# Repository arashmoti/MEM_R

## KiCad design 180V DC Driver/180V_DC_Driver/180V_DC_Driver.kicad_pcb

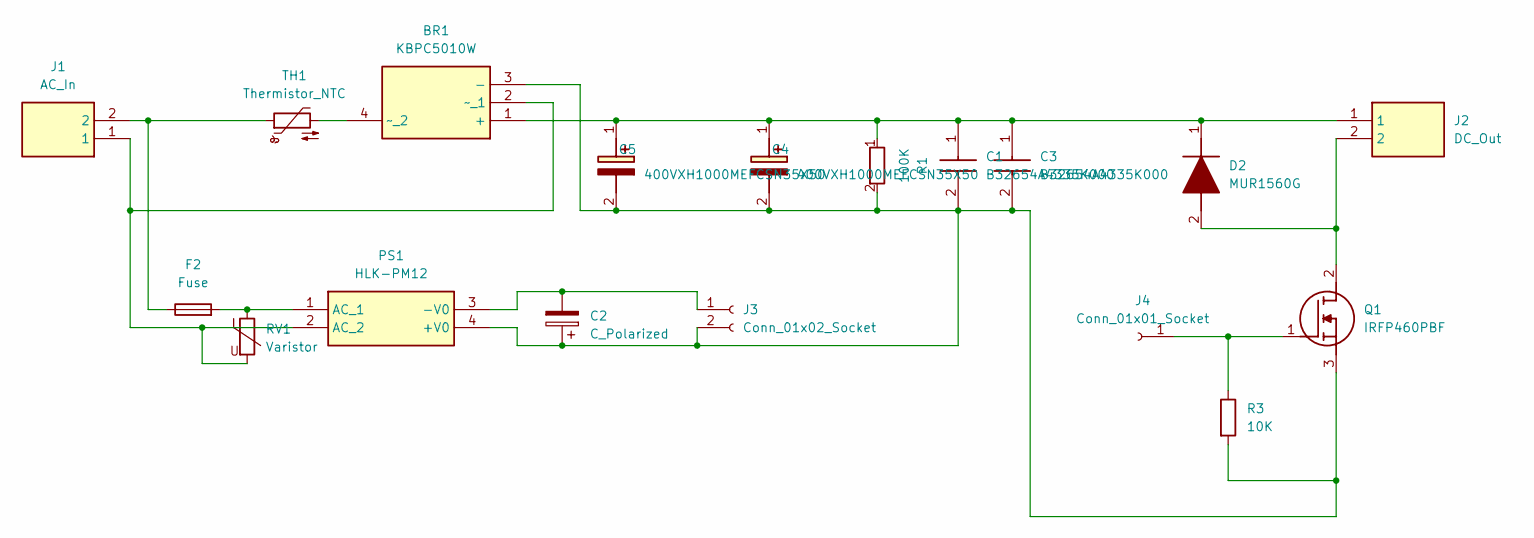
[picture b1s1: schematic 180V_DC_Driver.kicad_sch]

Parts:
BR1: KBPC5010W; Diode_Bridge_28.6x28.6x7.3mm_P18.0mm_P11.6mm; Manufacturer_Part_Number KBPC5010W; Mouser Part Number 905-KBPC5010W
C1, C3: B32654A4335K000; C_Rect_L31.5mm_W13.0mm_P27.50mm_MKS4; Manufacturer_Part_Number B32654A4335K000; Mouser Part Number 871-B32654A4335K
C2: C_Polarized; CP_Radial_D6.3mm_P2.50mm
C4, C5: 400VXH1000MEFCSN35X50; CP_Radial_D35.0mm_P10.00mm_SnapIn; Manufacturer_Part_Number 400VXH1000MEFCSN35X50
D2: MUR1560G; TO-220-2_Vertical; Manufacturer_Part_Number MUR1560G; Mouser Part Number 863-MUR1560G
F2: Fuse; PinHeader_1x02_P2.54mm_Vertical
J1: AC_In; TerminalBlock_Phoenix_MKDS-1,5-2-5.08_1x02_P5.08mm_Horizont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; Manufacturer_Part_Number 1935161; Mouser Part Number 651-1935161
J2: DC_Out; TerminalBlock_Phoenix_MKDS-1,5-2-5.08_1x02_P5.08mm_Horizont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; Manufacturer_Part_Number 1935161; Mouser Part Number 651-1935161
J3: Conn_01x02_Socket; PinHeader_1x02_P2.54mm_Vertical
J4: Conn_01x01_Socket; PinHeader_1x01_P2.54mm_Vertical
PS1: HLK-PM12; Converter_ACDC_Hi-Link_HLK-PMxx; Manufacturer_Part_Number HLK-PM12
Q1: IRFP460PBF; TO-247-3_Vertical; Manufacturer_Part_Number IRFP460PBF; Mouser Part Number 844-IRFP460PBF
R1: 100K; R_Axial_DIN0207_L6.3mm_D2.5mm_P10.16mm_Horizontal
R3: 10K; R_Axial_DIN0207_L6.3mm_D2.5mm_P10.16mm_Horizontal
RV1: Varistor; C_Disc_D10.5mm_W5.0mm_P5.00mm
TH1: Thermistor_NTC; C_Disc_D16.0mm_W5.0mm_P10.00mm

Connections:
unnamed: BR1.1 (+), C1.1, C3.1, C4.1 (+), C5.1 (+), D2.1 (K), J2.1, R1.1
unnamed: BR1.3 (-), C1.2, C2.1, C3.2, C4.2 (-), C5.2 (-), J3.2, PS1.4 (+V0), Q1.3 (S), R1.2, R3.2
unnamed: BR1.2 (~_1), J1.1, PS1.2 (AC_2), RV1.2
unnamed: BR1.4 (~_2), TH1.2
unnamed: D2.2 (A), J2.2, Q1.2 (D)
unnamed: F2.1, J1.2, TH1.1
unnamed: C2.2, J3.1, PS1.3 (-V0)
unnamed: J4.1 (Pin_1_1), Q1.1 (G), R3.1
unnamed: F2.2, PS1.1 (AC_1), RV1.1

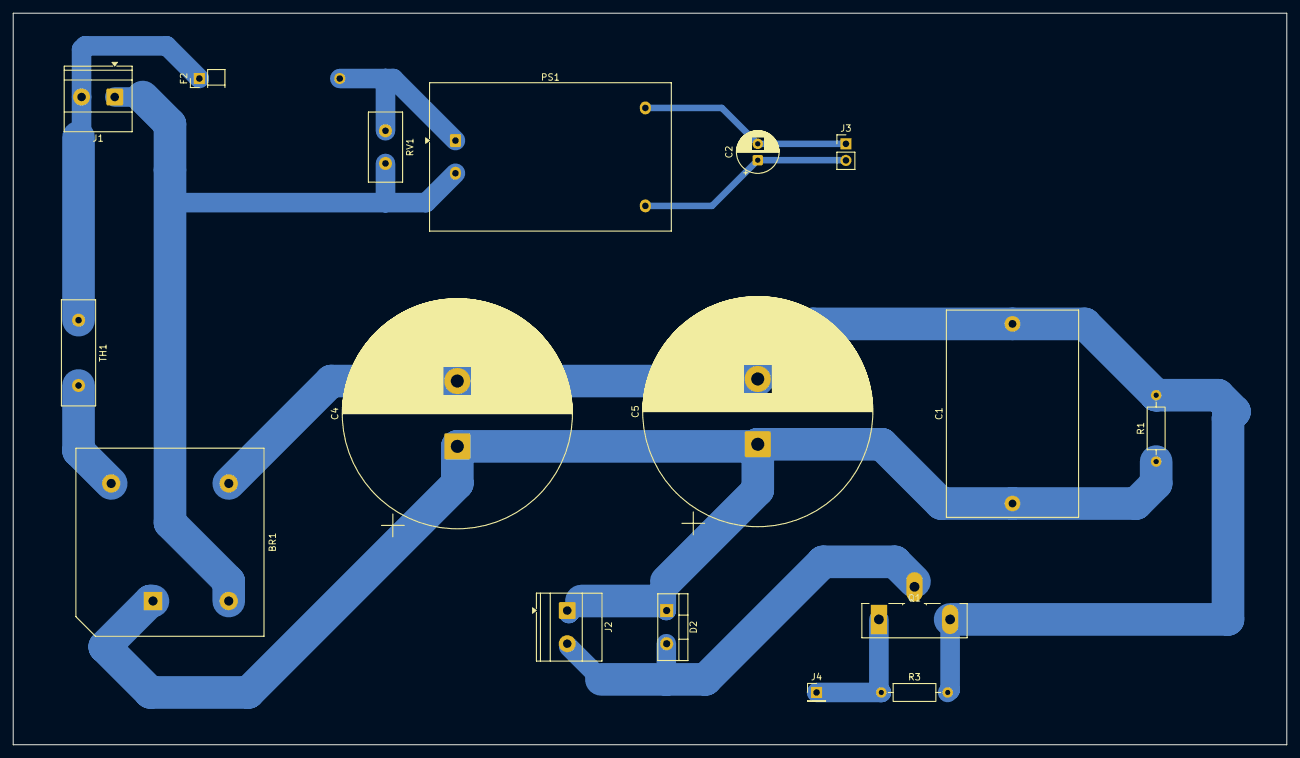
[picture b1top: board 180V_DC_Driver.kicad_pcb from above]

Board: 2 copper layers, 195.0 x 112.0 mm, 17 parts (0 on the bottom side), 9 nets.

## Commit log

2026-03-10 meeting 1
2026-03-10 Update notlar.md
    ama dedik
2026-03-17 c2c
    c2
2026-03-17 C3
    C3
2026-03-24 Create meeting3.md
    c4
2026-03-24 Update notlar.md
    3. hafta
2026-03-31 not4
2026-04-05 driver_dc_motor_sim
2026-04-13 13.04
2026-04-21 c2104
2026-05-05 c05.05
2026-06-02 c2.06
2026-06-18 c1806
2026-06-22 c22.06
2026-06-28 c28.06
